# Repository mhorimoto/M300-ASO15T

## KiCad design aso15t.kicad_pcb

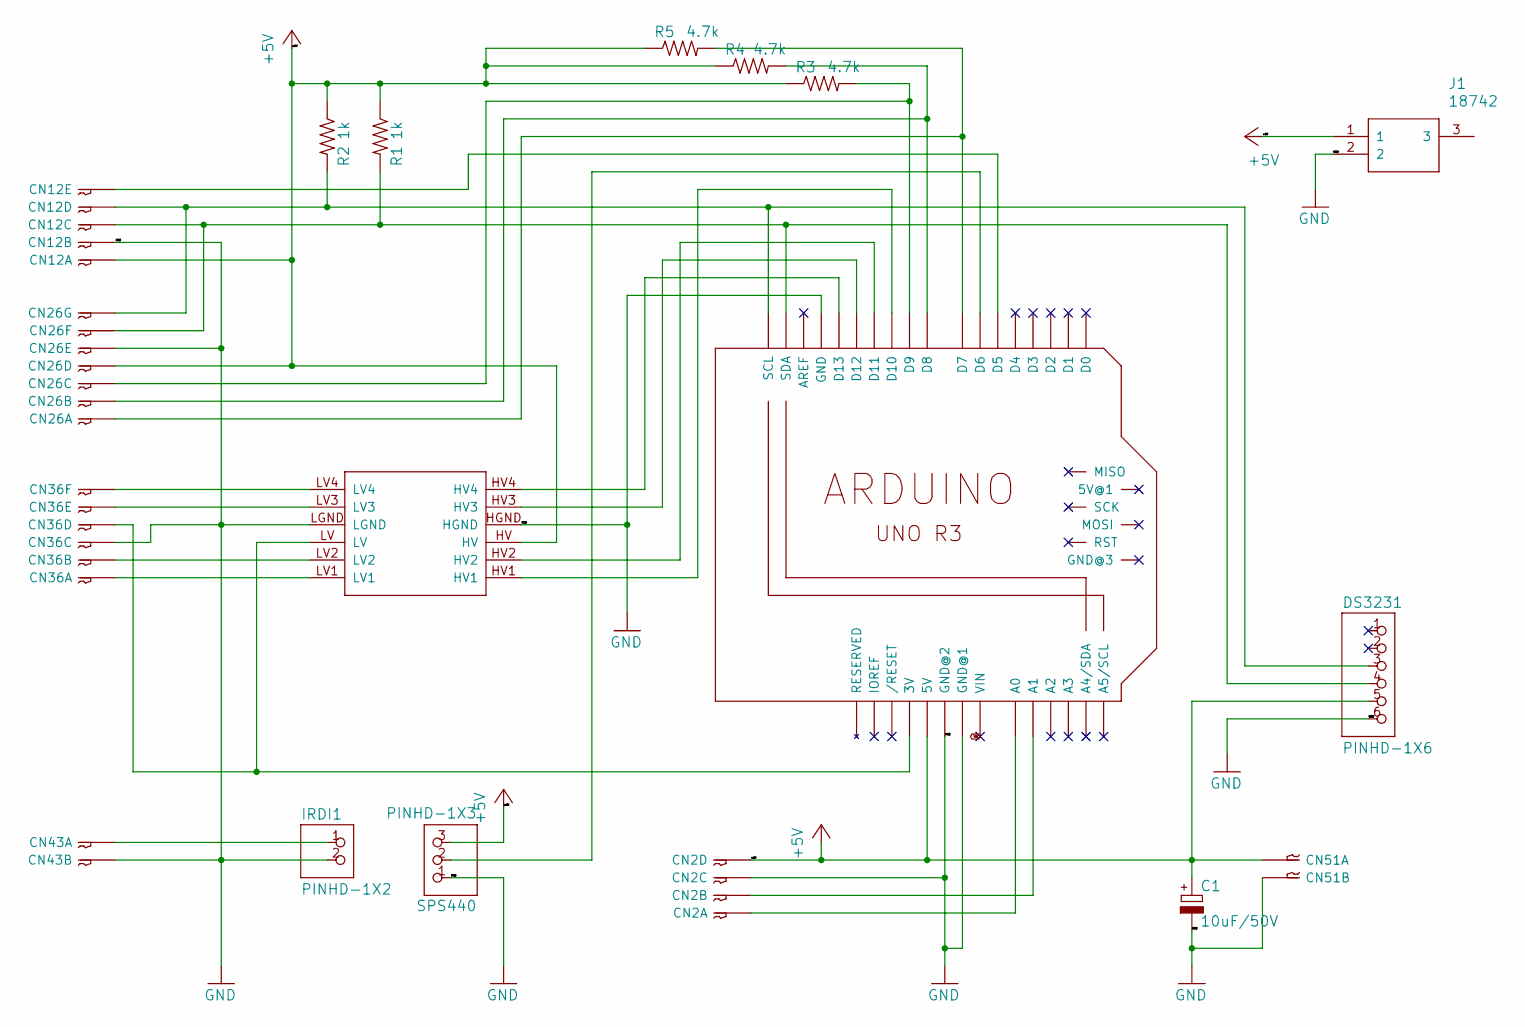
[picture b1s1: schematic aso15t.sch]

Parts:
C1: 10uF/50V; E2,5-5
CN2: CN02-HX711; B4B-XH
CN12: CN12-I2C-LCD; B5B-XH
CN26: CN26-I2C-S300; B7B-XH
CN36: CN36-IM920; B6B-XH
CN43: CN43-REMOCON; B2B-XH
CN51: CN51-FAN-PWR; B2B-XH
DS3231: PINHD-1X6; 1X06
IRDI1: PINHD-1X2; 1X02
J1: 18742
M1: ARDUINO_R3_ICSP; ARDUINOR3_ICSP
R1, R2: 1k; 0207_7
R3, R4, R5: 4.7k; 0207_7
SPS440: PINHD-1X3; 1X03
U$1: SFE-BOB-12009

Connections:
+5V: C1.+, CN2.P$4, CN12.P$1, CN26.P$4, CN51.P$1, DS3231.5, J1.1, M1.5V, R1.1, R2.1, R3.1, R4.1, R5.1, SPS440.3, U$1.HV
GND: C1.-, CN2.P$3, CN12.P$2, CN26.P$5, CN36.P$3, CN43.P$2, CN51.P$2, DS3231.6, IRDI1.2, J1.2, M1.GND, M1.GND@1 (GND@2), M1.GND@3 (GND@1), SPS440.1, U$1.HGND, U$1.LGND
unnamed: CN2.P$1, M1.A0
unnamed: CN2.P$2, M1.A1
unnamed: CN12.P$3, CN26.P$6, DS3231.4, M1.SDA, R1.2
unnamed: CN12.P$4, CN26.P$7, DS3231.3, M1.SCL, R2.2
unnamed: CN12.P$5, M1.D5
unnamed: CN26.P$1, M1.D7, R5.2
unnamed: CN26.P$2, M1.D8, R4.2
unnamed: CN26.P$3, M1.D9, R3.2
unnamed: CN36.P$1, U$1.LV1
unnamed: CN36.P$2, U$1.LV2
unnamed: CN36.P$4, M1.3V, U$1.LV
unnamed: CN36.P$5, U$1.LV3
unnamed: CN36.P$6, U$1.LV4
unnamed: CN43.P$1, IRDI1.1
unnamed: M1.D6, SPS440.2
unnamed: M1.D10, U$1.HV1
unnamed: M1.D11, U$1.HV2
unnamed: M1.D12, U$1.HV3
unnamed: M1.D13, U$1.HV4
VIN: M1.VIN

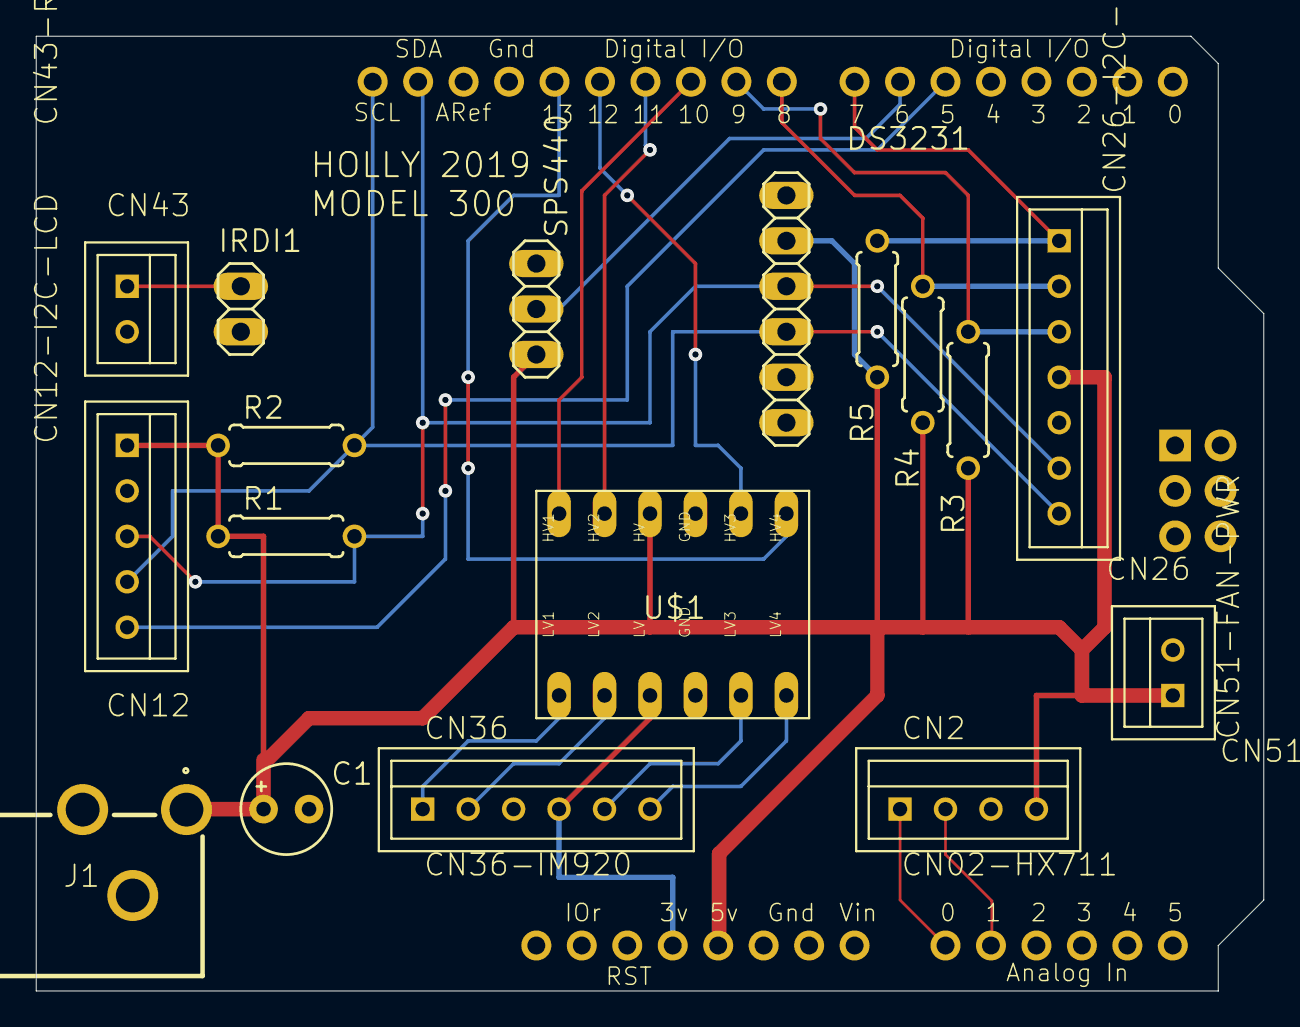
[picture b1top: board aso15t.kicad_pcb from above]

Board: 2 copper layers, 68.6 x 53.3 mm, 18 parts (0 on the bottom side), 21 nets.
